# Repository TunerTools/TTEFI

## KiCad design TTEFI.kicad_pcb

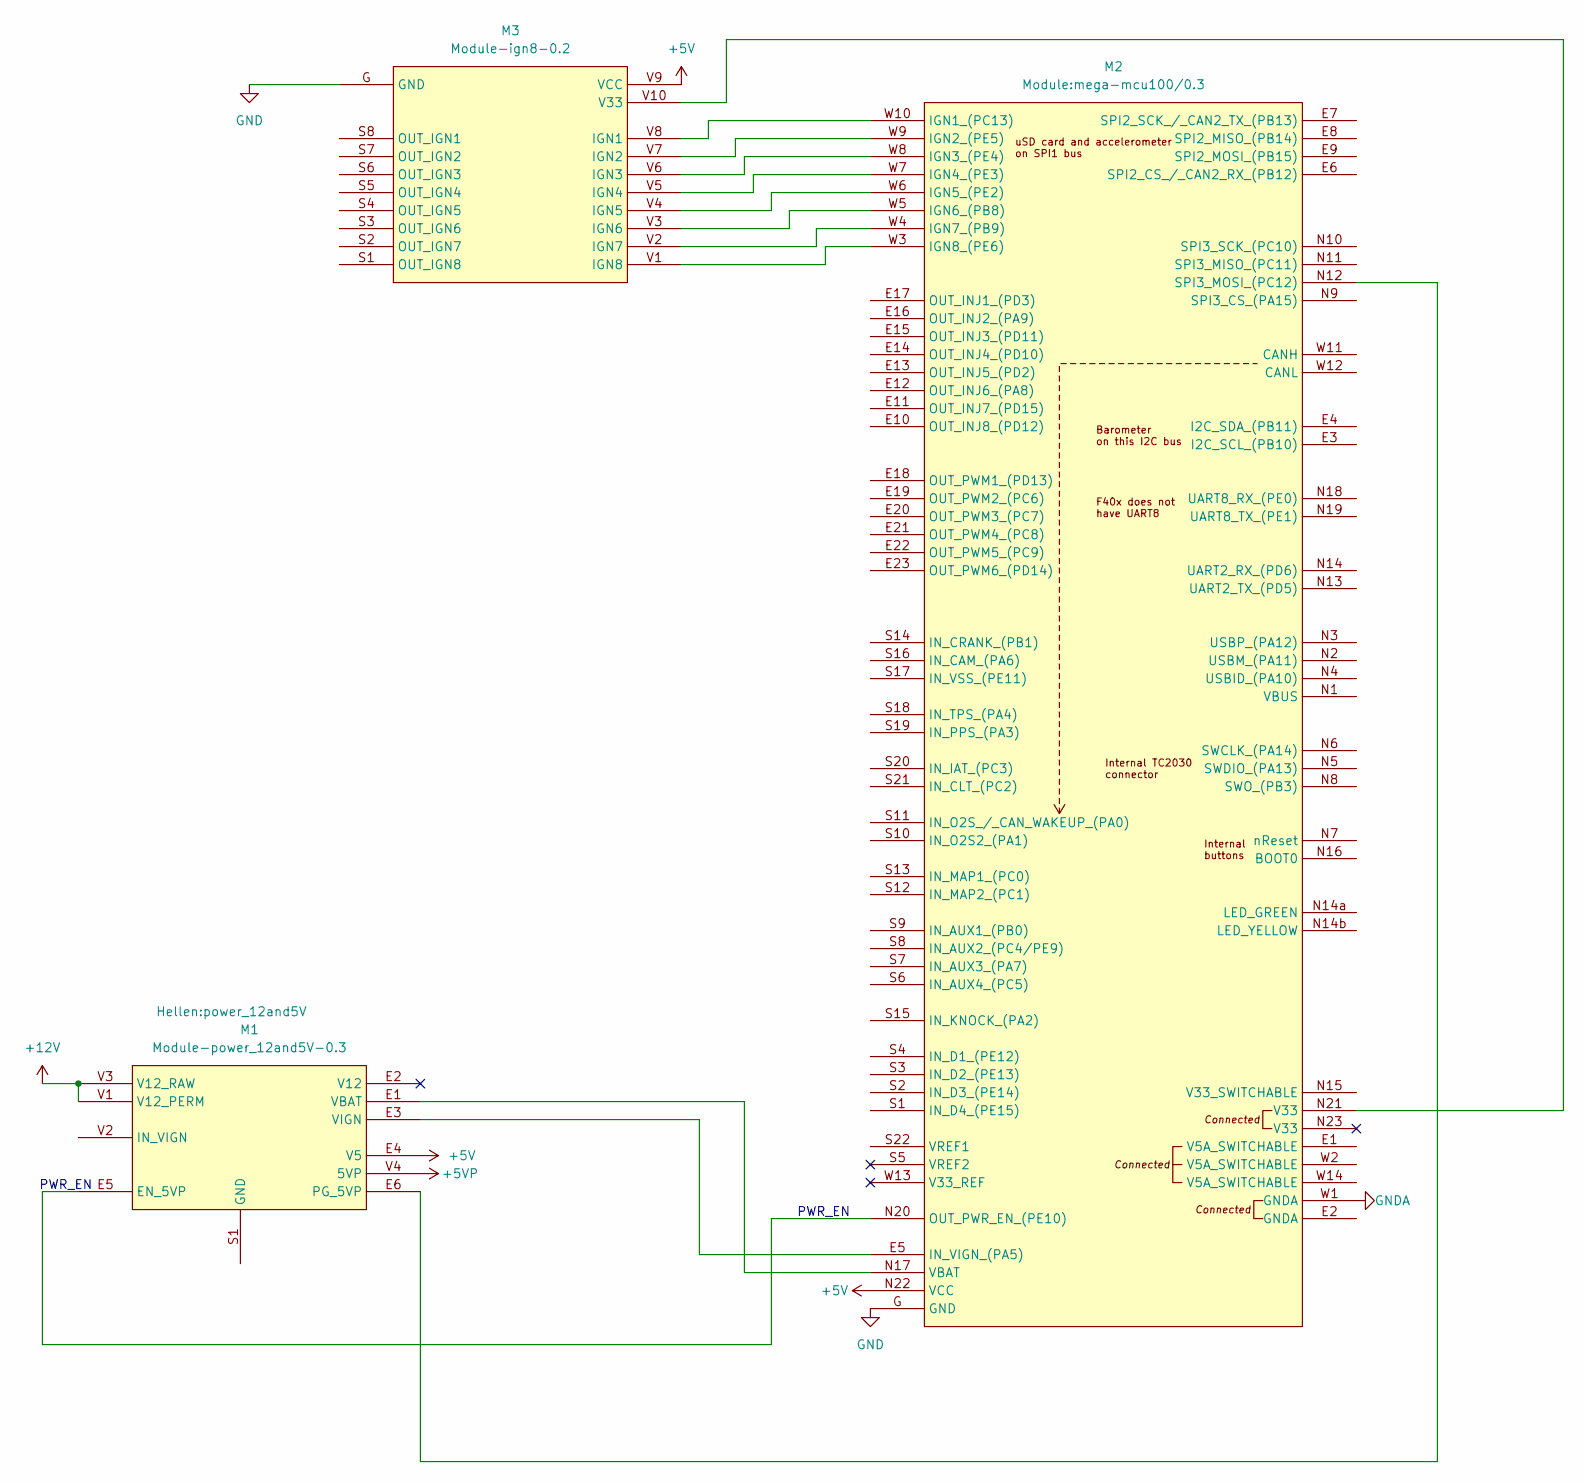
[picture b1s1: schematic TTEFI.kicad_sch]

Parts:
M1: Module-power_12and5V-0.3; power_12and5V
M2: Module:mega-mcu100/0.3; mega-mcu100
M3: Module-ign8-0.2; ign8

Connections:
+5V: M1.E4 (V5), M2.N22 (VCC), M3.V9 (VCC)
+5VP: M1.V4 (5VP)
+12V: M1.V1 (V12_PERM), M1.V3 (V12_RAW)
GND: M2.G (GND), M3.G (GND)
GNDA: M2.W1 (GNDA)
unnamed: M1.E5 (EN_5VP), M2.N20 (OUT_PWR_EN_(PE10))
unnamed: M1.E6 (PG_5VP), M2.N12 (SPI3_MOSI_(PC12))
unnamed: M1.E1 (VBAT), M2.N17 (VBAT)
unnamed: M1.E3 (VIGN), M2.E5 (IN_VIGN_(PA5))
unnamed: M2.W10 (IGN1_(PC13)), M3.V8 (IGN1)
unnamed: M2.W9 (IGN2_(PE5)), M3.V7 (IGN2)
unnamed: M2.W8 (IGN3_(PE4)), M3.V6 (IGN3)
unnamed: M2.W7 (IGN4_(PE3)), M3.V5 (IGN4)
unnamed: M2.W6 (IGN5_(PE2)), M3.V4 (IGN5)
unnamed: M2.W5 (IGN6_(PB8)), M3.V3 (IGN6)
unnamed: M2.W4 (IGN7_(PB9)), M3.V2 (IGN7)
unnamed: M2.W3 (IGN8_(PE6)), M3.V1 (IGN8)
unnamed: M2.N21 (V33), M3.V10 (V33)

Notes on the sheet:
PWR_EN

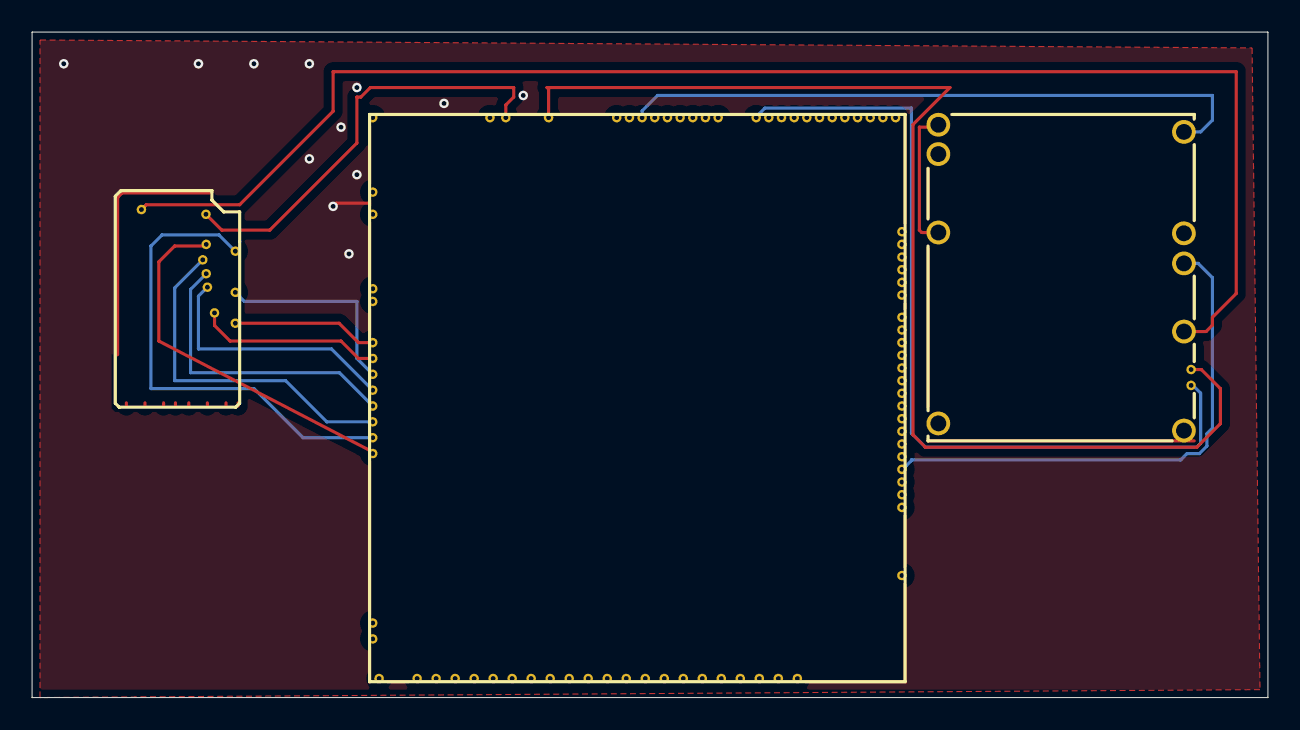
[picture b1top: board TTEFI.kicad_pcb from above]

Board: 2 copper layers, 78.0 x 42.0 mm, 3 parts (0 on the bottom side), 16 nets.

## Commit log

2025-11-10 GHA says update hellen-one
